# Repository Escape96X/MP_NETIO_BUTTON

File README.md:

# Manual
## How to install on esp8266 with Netio ESP flasher
Best method is to use Visual studio code with plugin Platformio.  
1. Download 'Kód' folder of this repository
2. After installation of VS code and Platformio override esptool.py in platformio
	- Windows path: C:\Users\\**username**\\.platformio\packages\tool-esptoolpy\esptool.py
3. Connect
	- Rx to Tx
	- Tx to Rx
	- GND to GND
	- PROG to PIO0
	- <a href = 'https://github.com/jiricmi/MP_NETIO_BUTTON/issues/14#issuecomment-888953459'>3,3 V to 3,3 V (You have to solder that to R2)</a>
	- <a href = 'https://github.com/jiricmi/MP_NETIO_BUTTON/issues/14#issuecomment-888953459'>RST to ESPEN (solder to RST button)</a>
4. Upload with platformio

<h2>NETIO button tutorial</h2>
<h3>How to set it up</h3>
<ol>
<li>Turn it on with ON/OFF switch</li>
<li>Hold both buttons until red light blinks once.</li>
<li>Open WiFi manager and find <b>NETIO-BUTTON</b> network and search <b>192.168.4.1</b> in internet browser</li>
<li>Under WiFis find your WiFi and click on it after that enter your password</li>
<li>After connecting, copy IP address of the device, reconnect to your network and enter new IP to your browser</li>
</ol>
<h3>Connect to Netio socket</h3>
<ol>
<li>Select <b>Action list</b> on main screen</li>
<li>Click on button <b>add</b></li>
<li>Enter IP adress of Netio socket (only IP without http:// or /netio.json)</li>
<li>Enter JSON string</li>
<li>Choose which button should use this command and submit</li>
<li> You can delete each record in table by clicking on button <b>Delete</b>
<li> On main screen click on button <b>Deep sleep</b> to end <b>conf-mode</b>
</ol>

<h2>Basic info</h2>
<p>
This is prototype of NETIO button that allow you to control the NETIO socket.
It works on sending HTTP request method.
On the other side, this communication is handled by the socket via JSON API. Button is made with small consumption. Button is only up when user sends HTTP request or turns on conf-mode.
</p>
<h3>Device structure</h3>
<p>
Device has 2 buttons with S1 and S2 marks. They are used for <b>JSON configure</b>.
User can program those buttons via conf-mode. <br>
</p>
<h3>LED and buzzer signaling</h3>
<p>
Device has LED with green and red color.
Buzzer is connected with red color of LED.<br>
If <b>green light</b> is on, device is trying to connect to wlan or communicate with the socket. <br>
If <b>red light</b> blinks once for longer time, device entered or quited conf-mode.<br> 
If <b>red light</b> blinks 2x with buzzer signalization, connection to wlan failed. <br>
If <b>red light</b> blinks 3x with buzzer signalization, HTTP communication failed.
Probably IP address of the socket is invalid. <br>
If <b>red light</b> blinks 4x with buzzer signalization, device wasn't able to recognize input. Please hold the button little bit longer.
</p>
<h2>Conf-mode</h2>
<p>
For entering conf-mode, hold both buttons until light turn on for 400ms. After that connect to AP called <b>NETIO-BUTTON</b>. Open browser and search <b>192.168.4.1</b>.
</p>
<h3>WiFi selection</h3>
<p>
On main screen, user is able to connect device to any close-range network without security or with WES, WPA or WPA2-personal. For update WiFi list, click on <b>Scan</b> button. <br>
By clicking on button with your wanted network, you will be transfer to security page (only if network is secured). If password is checked, page will show you IP address of device selected by DHCP server in network. And now you are able to connect to conf-mode via your network and appropriate IP address.
</p>
<h3>IP address of the socket</h3>
<p>
User is able to set 10 IP addresses for each button. So one HTTP request will be send a maximum of 10 devices at once. You can add IP address via form where you also select with button should use this IP address. It is possible to delete each address.
</p>
<h3>JSON message</h3>
<p>
Behind button configure you can find feature to write JSON message to JSON API of socket. Current JSON is below the form.
</p>
<h3>Disable conf-mode button</h3>
<p>This button will put device to sleep. Holding both buttons during conf-mode has same effect.</p>
<h3>Factory reset button</h3>
<p>Deletes whole EEPROM.</p>

# Obsah
📦MP_NETIO_BUTTON  
 ┣ 📂kod - - **Finální program**  
 ┣ 📂dokumentace - **Dokumentace s latex soubory**  
 ┃ ┗ 📜document.pdf   
 ┣ 📂mereni - **Waveform a screenshoty**    
 ┃ ┣ 📂esp32  
 ┃ ┃ ┣ 📂operace  
 ┃ ┃ ┣ 📂ustalene_stavy  
 ┃ ┃ ┗ 📜vysledky_mereni_esp32.xlsx  
 ┃ ┗ 📂esp8266  
 ┃ ┃ ┣ 📂operace  
 ┃ ┃ ┣ 📂ustalene_stavy  
 ┃ ┃ ┗ 📜vysledky_mereni_esp8266.xlsx  
 ┣ 📂navrh_vzorku - **Eagle**    
 ┃ ┣ 📂esp32  
 ┃ ┗ 📂esp8266  
 ┣ 📜.gitignore  
 ┗ 📜README.md  
# Poděkování
*Chtěl bych poděkovat panu učiteli Ing. Břetislavu Bakalovi za odborné vedení práce
a cenné rady, které mi pomohly tuto práci zkompletovat. Rád bych také poděkoval technickému řediteli Ing. Břetislavu Bakalovi ml. společnosti NETIO products a.s. za cenné
rady, věcné připomínky a vstřícnost při konzultacích a vypracování maturitní práce*.
# Úvod maturitní práce
V této maturitní práci porovnám platformy ESP8266 a ESP32 z hlediska spotřeby a reakčního času v takových podmínkách, aby bylo možné určit platformu, která je vhodnější pro funkční vzorek ovladače zásuvek od společnosti NETIO Products a. s. Jelikož je cílem vytvořit co nejvíce úsporné zařízení, jak je jen možné, budu porovnávat jednotlivé ustálené stavy. Zařízení také musí být uživatelsky přívětivé, tzn. není ideální, když
uživatel musí čekat na reakci několik sekund.

Dále na každé platformě porovnám rychlost a spotřebu připojení k WiFi síti a následné odeslání HTTP requestu.
Po vybrání vhodné metody ustáleného stavu, vytvořím konfigurační rozhraní pro editaci nastavení sítě a HTTP requestu, do kterého se bude přistupovat přes access point zařízení ESP.  

Ve finále vytvořím dva funkční koncepty ovladačů pro každou platformu. Tento koncept
bude vycházet z předchozího měření a zjištění. Funkčním vzorkem bude možné ovládat,
buď dvě různé zásuvky, nebo jednu zásuvku z dvěma výstupy. V závěru práce zhodnotím,
zda je možné vytvořit plnohodnotný produkt, či nikoliv.

# Zadání maturitní práce

- V dokumentaci popište technologie NETIO, ESP8266 a ESP32 s ohledem na požadované funkce ovladače
- Navrhněte vhodné uživatelsky přívětivé rozhraní pro konfiguraci ovladače a jeho
připojení do WiFi sítě
- Realizujte požadované funkce na ovladač:
	- vstup na 2 nezávislá tlačítka pro standardní dvojitý přepínač/spínač dvou samostatných zásuvek jednoho zařízení NETIO, eliminace rychlých mačkání (nervózní uživatel)
	- nepodařený příkaz/přepnutí vypínače (nepodaří se odeslat příkaz http) je indikován bliknutím LED a pípnutím buzzeru. Kontroluje se odpověď http serveru (např. 200, 404 návratové hodnoty)
	- Zvolte vhodnou technologii výroby funkčních vzorků (nepájivé pole, DPS) a vyrobte jeden funkční vzorek na bázi ESP8266 a druhý na bázi ESP32 s možností měření odebíraného proudu
	- Určete vhodnou metodu měření dynamické spotřeby energie v čase (reakční doby) pro různé režimy připojení, způsobu komunikace a platformy procesoru:
		- ESP je vypnuto a vzbudí se nějakým externím obvodem přes enable/reset vstup po stisku tlačítka
		- ESP je v deep sleep módu - low power režimu a vzbudí se tlačítkem
 		- ESP je kontinuálně zapnuto
		- Kolik energie spotřebují uvedené režimy při napájení z baterie. Výsledky měření názorně porovnejte
	- Celou dokumentaci včetně výpisů zdrojového programu s komentářem veďte ve verzovacím systému Git a elektronicky doložte k tištěné podobě dokumentace
## Kritéria funkčnosti
- vyrobené vzorky ovladače (ESP8266 a ESP32) jsou funkční
- je vytvořeno uživatelské rozhraní pro konfiguraci ovladač
- bylo provedeno měření spotřeby a doby odezvy pro oba typy ovladače

## Výstupy
- srovnání platforem ESP32 a ESP8266 s ohledem na požadované funkce
- návrh požadovaných funkcí ovladače
- návrh variant ovladače s platformou ESP32 a ESP8266 ve formě ověření konceptu
- zdrojové kódy v repozitáři GIT (GitHub nebo GitLab)
- schéma zapojeni všech zkoušených variant v řešení
- srovnání spotřeby a reakční doby funkčních vzorků

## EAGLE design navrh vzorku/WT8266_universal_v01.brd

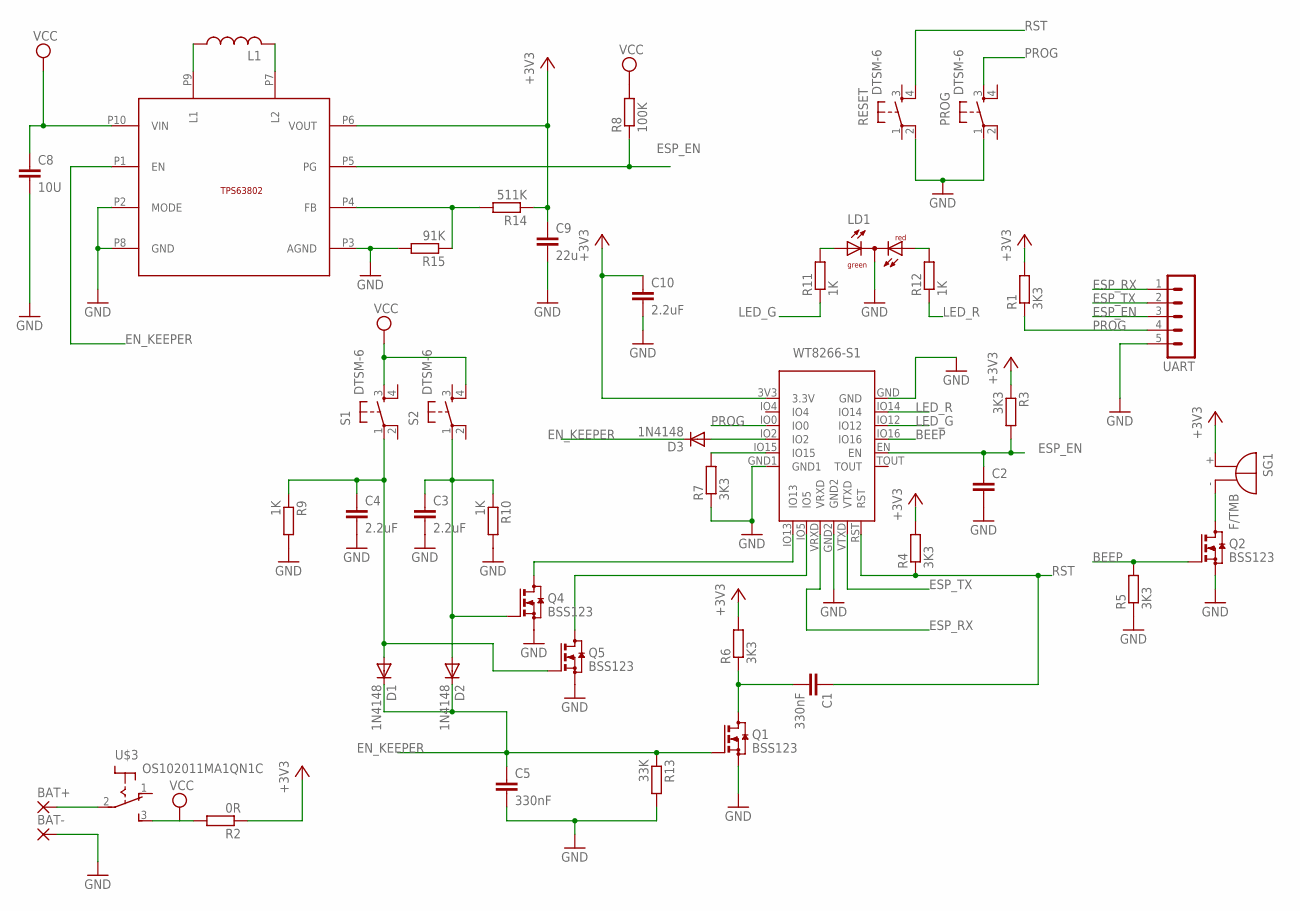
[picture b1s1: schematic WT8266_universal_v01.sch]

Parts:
BAT+: 2,54/1,0
BAT-: 2,54/1,0
C1, C5: 330nF; C0805
C2: C-EUC0805; C0805
C3, C4, C10: 2.2uF; C0805
C8: 10U; C0805
C9: 22u; C0805
D1, D2, D3: 1N4148; 0805
L1: L-USL2825P; L2825P
LD1: DUOLED-RG-C3MM; DUOLED-A-3MM
PROG: DTSM-6
Q1, Q2, Q4, Q5: BSS123; SOT23
R1, R3, R4, R5, R6, R7: 3K3; R0805
R2: 0R; R0805
R8: 100K; R0805
R9, R10, R11, R12: 1K; R0805
R13: 33K; R0805
R14: 511K; R0805
R15: 91K; R0805
RESET: DTSM-6
S1, S2: DTSM-6
SG1: F/TMB
U$1: WT8266-S1
U$3: OS102011MA1QN1C
U$4: TPS63802; VSON-HR-10
UART: MAR05-1

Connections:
+3V3: C9.1, C10.1, R1.2, R2.1, R3.1, R4.2, R6.2, R14.1, SG1.+, U$1.3V3 (3.3V), U$4.P6 (VOUT)
BEEP: Q2.1 (G), R5.2, U$1.IO16
EN_KEEPER: C5.1, D1.1 (C), D2.1 (C), D3.1 (C), Q1.1 (G), R13.1, U$4.P1 (EN)
ESP_EN: C2.1, R3.2, R8.1, U$1.EN, U$4.P5 (PG), UART.3
ESP_RX: U$1.VRXD, UART.1
ESP_TX: U$1.VTXD, UART.2
GND: BAT-.1, C2.2, C3.2, C4.2, C5.2, C8.2, C9.2, C10.2, LD1.2 (C), PROG.1, Q1.2 (S), Q2.2 (S), Q4.2 (S), Q5.2 (S), R5.1, R7.1, R9.2, R10.2, R13.2, R15.2, RESET.2, U$1.GND, U$1.GND1, U$1.GND2, U$4.P2 (MODE), U$4.P3 (AGND), U$4.P8 (GND), UART.5
LED_G: R11.1, U$1.IO12
LED_R: R12.1, U$1.IO14
unnamed: R14.2, R15.1, U$4.P4 (FB)
unnamed: C1.2, Q1.3 (D), R6.1
unnamed: R7.2, U$1.IO15
unnamed: D3.2 (A), U$1.IO2
unnamed: Q4.3 (D), U$1.IO13
unnamed: Q5.3 (D), U$1.IO5
unnamed: LD1.1 (AG), R11.2
unnamed: Q2.3 (D), SG1.-
unnamed: BAT+.1, U$3.2
unnamed: C3.1, D2.2 (A), Q4.1 (G), R10.1, S2.1
unnamed: L1.1, U$4.P9 (L1)
unnamed: C4.1, D1.2 (A), Q5.1 (G), R9.1, S1.1
unnamed: L1.2, U$4.P7 (L2)
unnamed: LD1.3 (AR), R12.2
PROG: PROG.3, R1.1, U$1.IO0, UART.4
RST: C1.1, R4.1, RESET.4, U$1.RST
VCC: C8.1, R2.2, R8.2, S1.3, S2.4, U$3.3 (S), U$4.P10 (VIN)

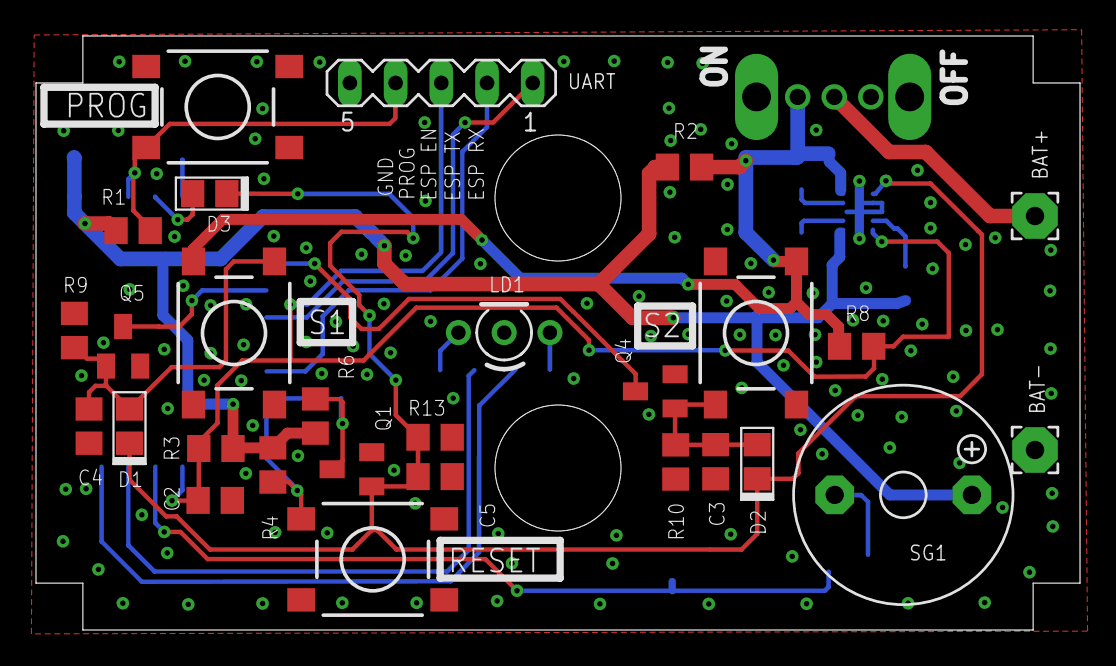
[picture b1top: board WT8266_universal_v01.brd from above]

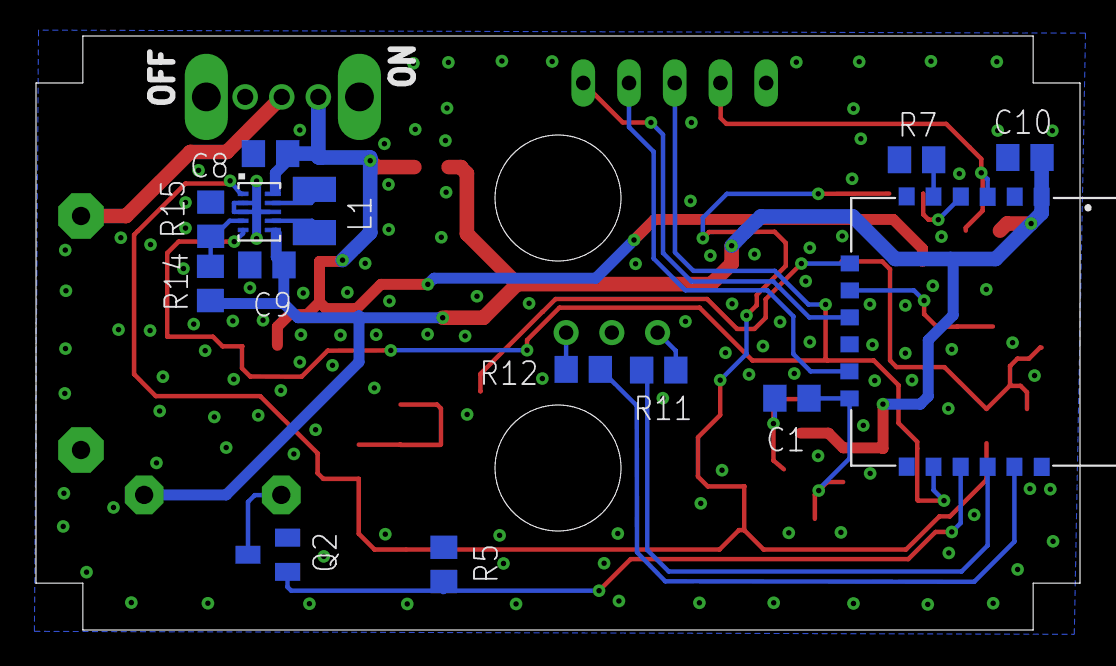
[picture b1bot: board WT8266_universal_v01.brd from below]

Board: 2 copper layers, 58.0 x 33.0 mm, 43 parts (14 on the bottom side), 26 nets.

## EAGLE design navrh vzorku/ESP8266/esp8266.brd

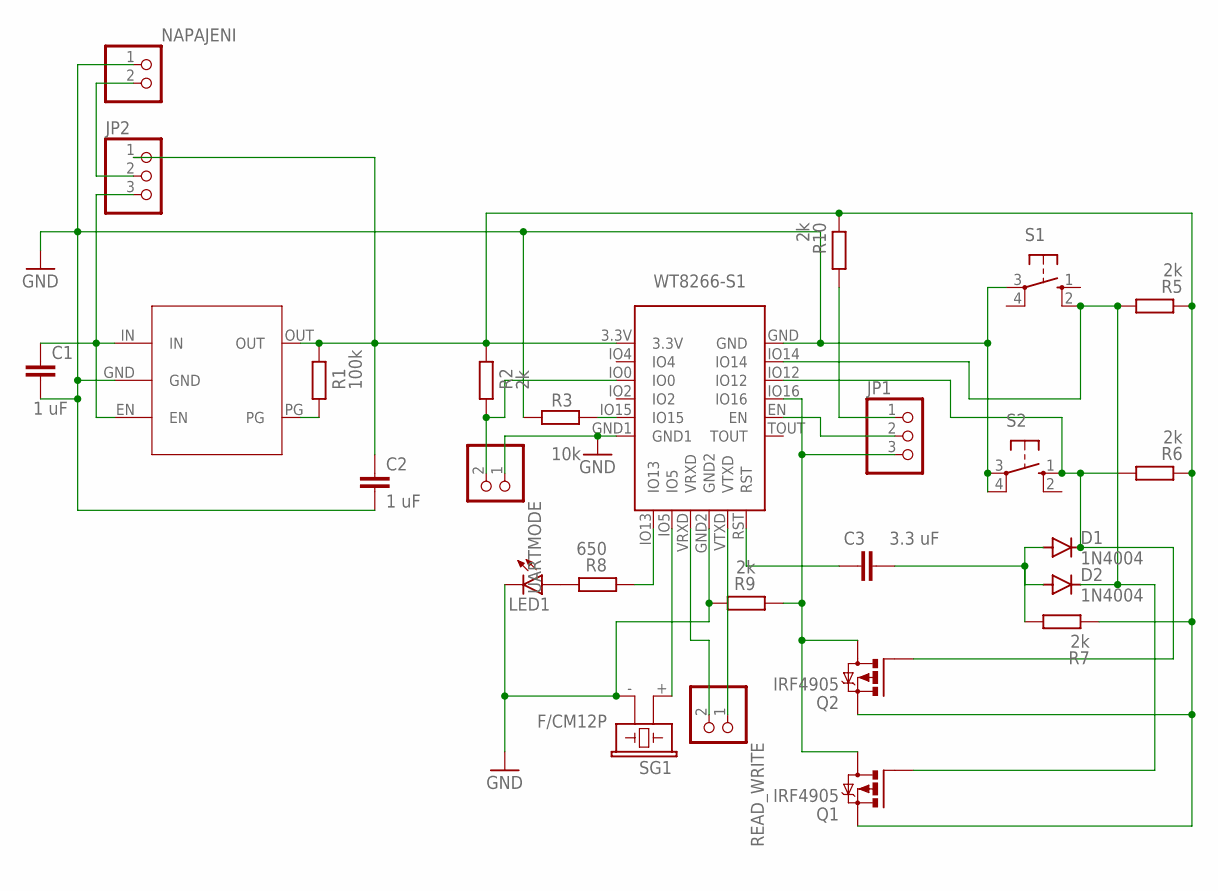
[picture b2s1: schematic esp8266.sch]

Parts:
C1, C2: 1 uF; C2.5-2
C3: 3.3 uF; C2.5-2
D1, D2: 1N4004; DO41-10
JP1, JP2: PINHD-1X3; 1X03
LED1: LED5MM
NAPAJENI: PINHD-1X2; 1X02
Q1, Q2: IRF4905; TO220BH
R1: 100k; 0207/10
R2, R5, R6, R7, R9, R10: 2k; 0207/10
R3: 10k; 0207/10
R8: 650; 0207/10
READ_WRITE: PINHD-1X2; 1X02
S1, S2: 10-XX; B3F-10XX
SG1: F/CM12P
U$1: WT8266-S1
U$2: LDLN030
UARTMODE: PINHD-1X2; 1X02

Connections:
GND: C1.2, C2.2, LED1.K (C), NAPAJENI.1, R3.1, R9.2, S1.3, S2.3, S2.4 (P1), SG1.- (2), U$1.GND, U$1.GND1, U$1.GND2, U$2.GND, UARTMODE.1
unnamed: C1.1, JP2.3, U$2.EN, U$2.IN
unnamed: JP2.2, NAPAJENI.2
unnamed: R2.1, U$1.IO0, UARTMODE.2
unnamed: R1.1, U$2.PG
unnamed: READ_WRITE.2, U$1.VRXD
unnamed: C2.1, JP2.1, Q1.S, Q2.S, R1.2, R2.2, R5.1, R6.1, R7.1, R10.1, U$1.3.3V, U$2.OUT
unnamed: READ_WRITE.1, U$1.VTXD
unnamed: R3.2, U$1.IO15
unnamed: C3.1, U$1.RST
unnamed: D1.C, Q2.G, R6.2, S2.1 (S), U$1.IO12
unnamed: D2.C, Q1.G, R5.2, S1.2 (S1), U$1.IO14
unnamed: C3.2, D1.A, D2.A, R7.2
unnamed: R8.1, U$1.IO13
unnamed: LED1.A, R8.2
unnamed: SG1.+ (1), U$1.IO5
unnamed: JP1.3, Q1.D, Q2.D, R9.1, U$1.IO16
unnamed: JP1.2, U$1.EN
unnamed: JP1.1, R10.2

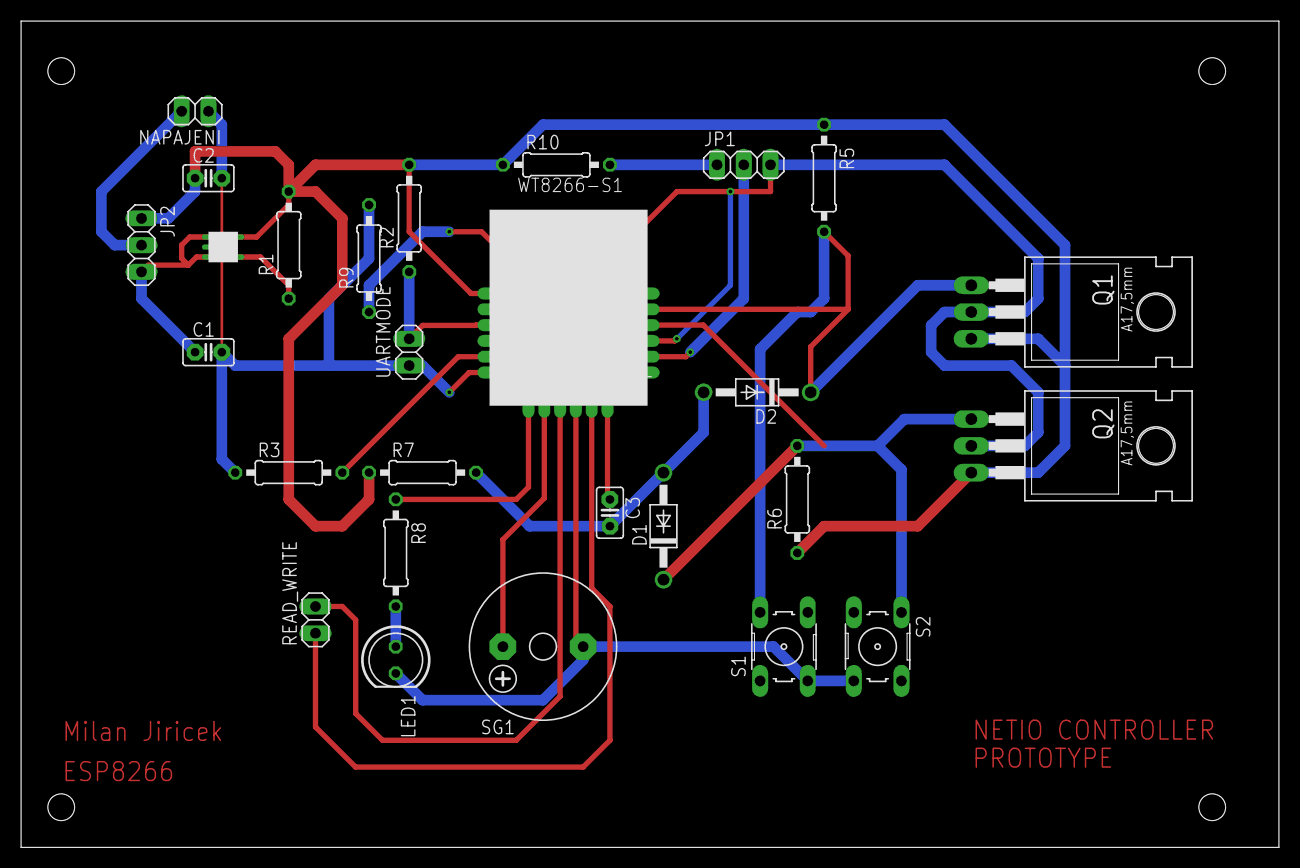
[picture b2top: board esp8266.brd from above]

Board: 2 copper layers, 119.4 x 78.4 mm, 27 parts (0 on the bottom side), 19 nets.

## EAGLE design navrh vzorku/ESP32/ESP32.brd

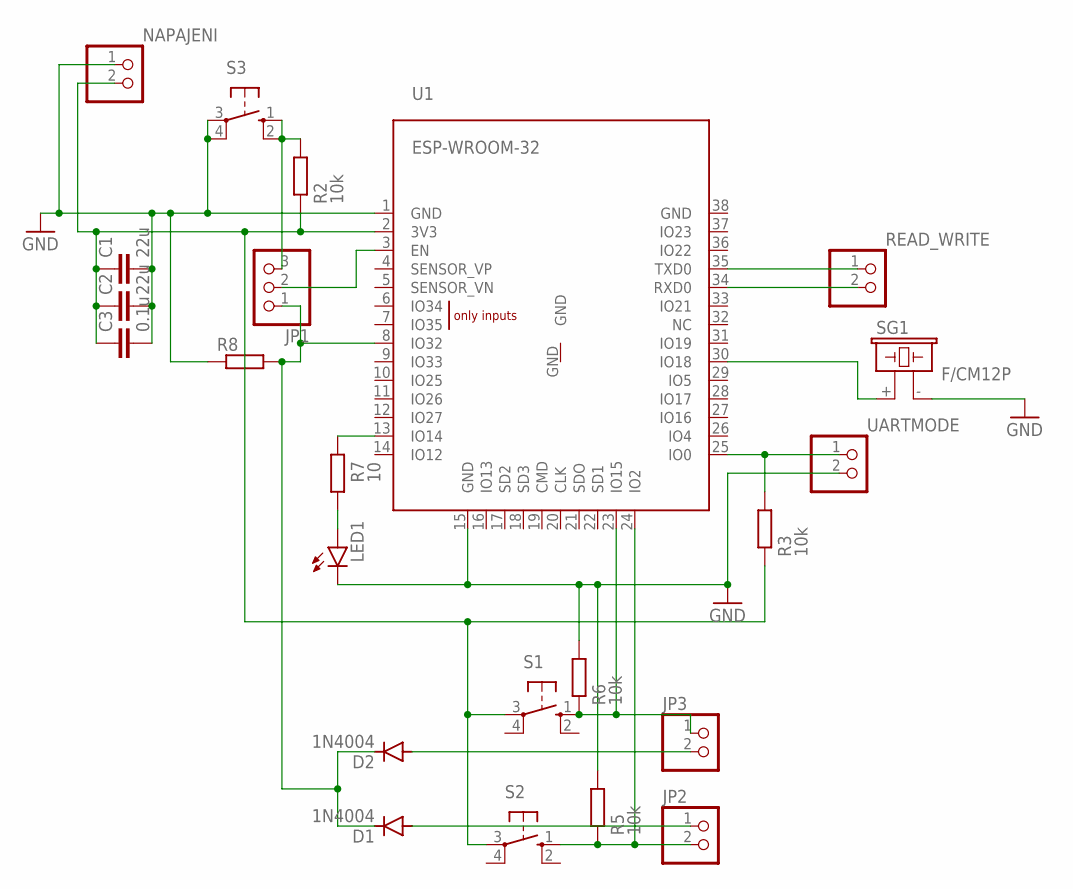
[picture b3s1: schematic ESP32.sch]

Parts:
C1, C2: 22u; C2.5-2
C3: 0.1u; C2.5-2
D1, D2: 1N4004; DO41-10
JP1: PINHD-1X3; 1X03
JP2, JP3: PINHD-1X2; 1X02
LED1: LED5MM
NAPAJENI: PINHD-1X2; 1X02
R2, R3, R5, R6: 10k; 0207/10
R7: 10; 0207/10
R8: R-EU_0207/10; 0207/10
READ_WRITE: PINHD-1X2; 1X02
S1, S2, S3: 10-XX; B3F-10XX
SG1: F/CM12P
U1: ESP-WROOM-32
UARTMODE: PINHD-1X2; 1X02

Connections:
GND: C1.2, C2.2, C3.2, LED1.K (C), NAPAJENI.1, R5.2, R6.2, R8.1, S3.3, S3.4 (P1), SG1.- (2), U1.1 (GND), U1.15 (GND), UARTMODE.2
unnamed: SG1.+ (1), U1.30 (IO18)
unnamed: C1.1, C2.1, C3.1, NAPAJENI.2, R2.1, R3.1, S1.3, S2.3, U1.2 (3V3)
unnamed: JP1.3, R2.2, S3.1 (S), S3.2 (S1)
unnamed: JP1.2, U1.3 (EN)
unnamed: READ_WRITE.2, U1.34 (RXD0)
unnamed: READ_WRITE.1, U1.35 (TXD0)
unnamed: R3.2, U1.25 (IO0), UARTMODE.1
unnamed: JP2.2, R5.1, S2.1 (S), U1.24 (IO2)
unnamed: JP3.1, R6.1, S1.1 (S), U1.23 (IO15)
unnamed: R7.2, U1.13 (IO14)
unnamed: LED1.A, R7.1
unnamed: D1.C, D2.C, JP1.1, R8.2, U1.8 (IO32)
unnamed: D1.A, JP2.1
unnamed: D2.A, JP3.2

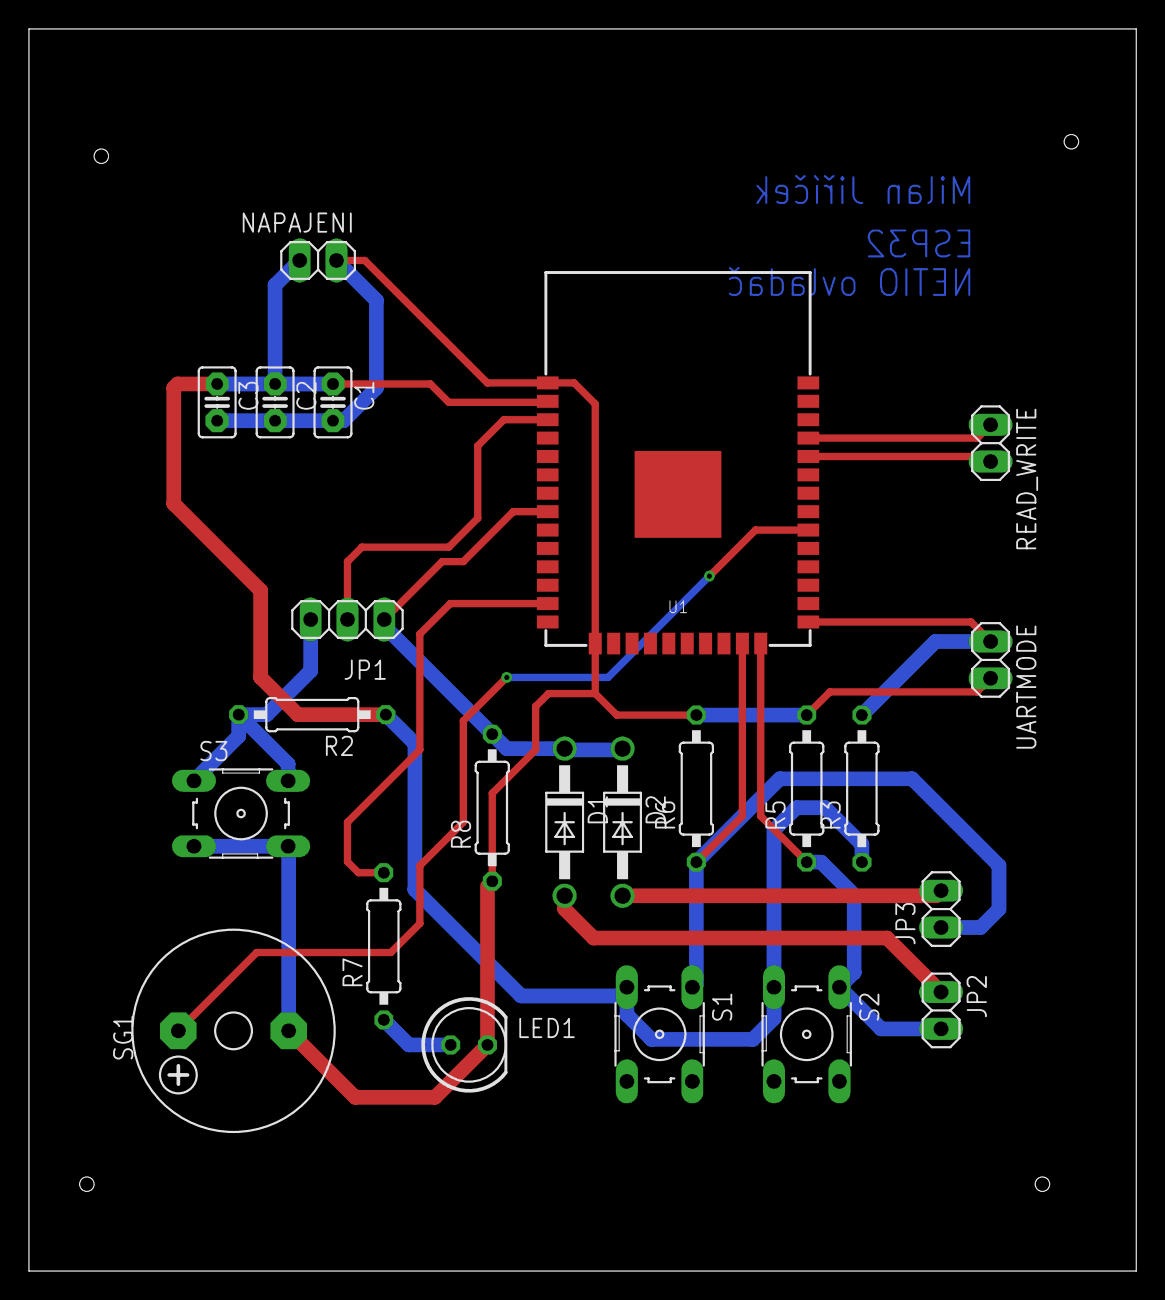
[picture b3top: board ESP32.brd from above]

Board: 2 copper layers, 76.5 x 85.8 mm, 23 parts (0 on the bottom side), 15 nets.

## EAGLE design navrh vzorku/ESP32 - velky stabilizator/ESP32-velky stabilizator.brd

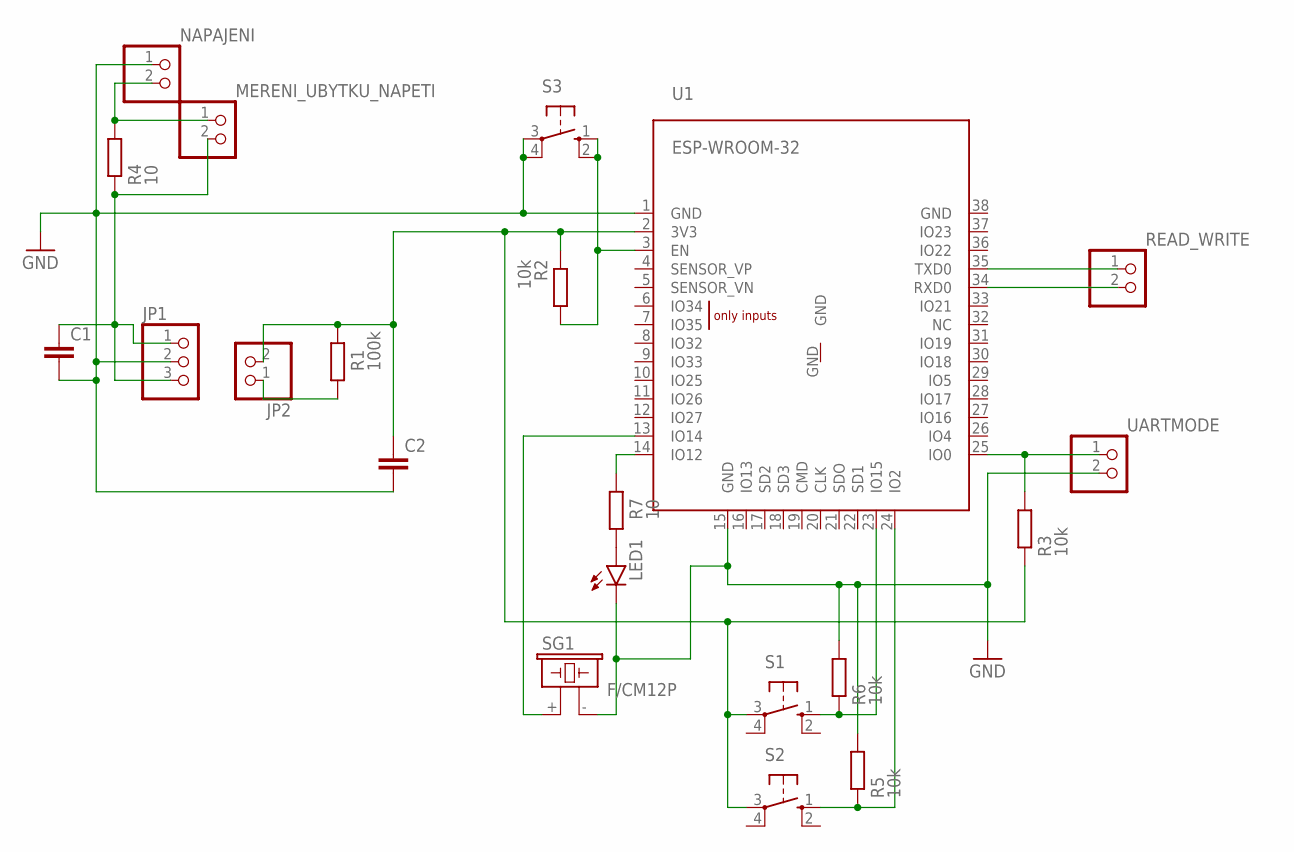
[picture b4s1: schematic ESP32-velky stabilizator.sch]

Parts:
C1, C2: C2.5/2; C2.5-2
JP1: PINHD-1X3; 1X03
JP2: PINHD-1X2; 1X02
LED1: LED5MM
MERENI_UBYTKU_NAPETI: PINHD-1X2; 1X02
NAPAJENI: PINHD-1X2; 1X02
R1: 100k; 0207/10
R2, R3, R5, R6: 10k; 0207/10
R4, R7: 10; 0207/10
READ_WRITE: PINHD-1X2; 1X02
S1, S2, S3: 10-XX; B3F-10XX
SG1: F/CM12P
U1: ESP-WROOM-32
UARTMODE: PINHD-1X2; 1X02

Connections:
GND: C1.2, C2.2, JP1.2, LED1.K (C), NAPAJENI.1, R5.2, R6.2, S3.3, S3.4 (P1), SG1.- (2), U1.1 (GND), U1.15 (GND), UARTMODE.2
unnamed: C1.1, JP1.1, JP1.3, MERENI_UBYTKU_NAPETI.2, R4.1
unnamed: C2.1, JP2.2, R1.2, R2.1, R3.1, S1.3, S2.3, U1.2 (3V3)
unnamed: JP2.1, R1.1
unnamed: R2.2, S3.1 (S), S3.2 (S1), U1.3 (EN)
unnamed: READ_WRITE.2, U1.34 (RXD0)
unnamed: READ_WRITE.1, U1.35 (TXD0)
unnamed: R3.2, U1.25 (IO0), UARTMODE.1
unnamed: R7.2, U1.14 (IO12)
unnamed: MERENI_UBYTKU_NAPETI.1, NAPAJENI.2, R4.2
unnamed: R5.1, S2.1 (S), U1.24 (IO2)
unnamed: R6.1, S1.1 (S), U1.23 (IO15)
unnamed: SG1.+ (1), U1.13 (IO14)
unnamed: LED1.A, R7.1

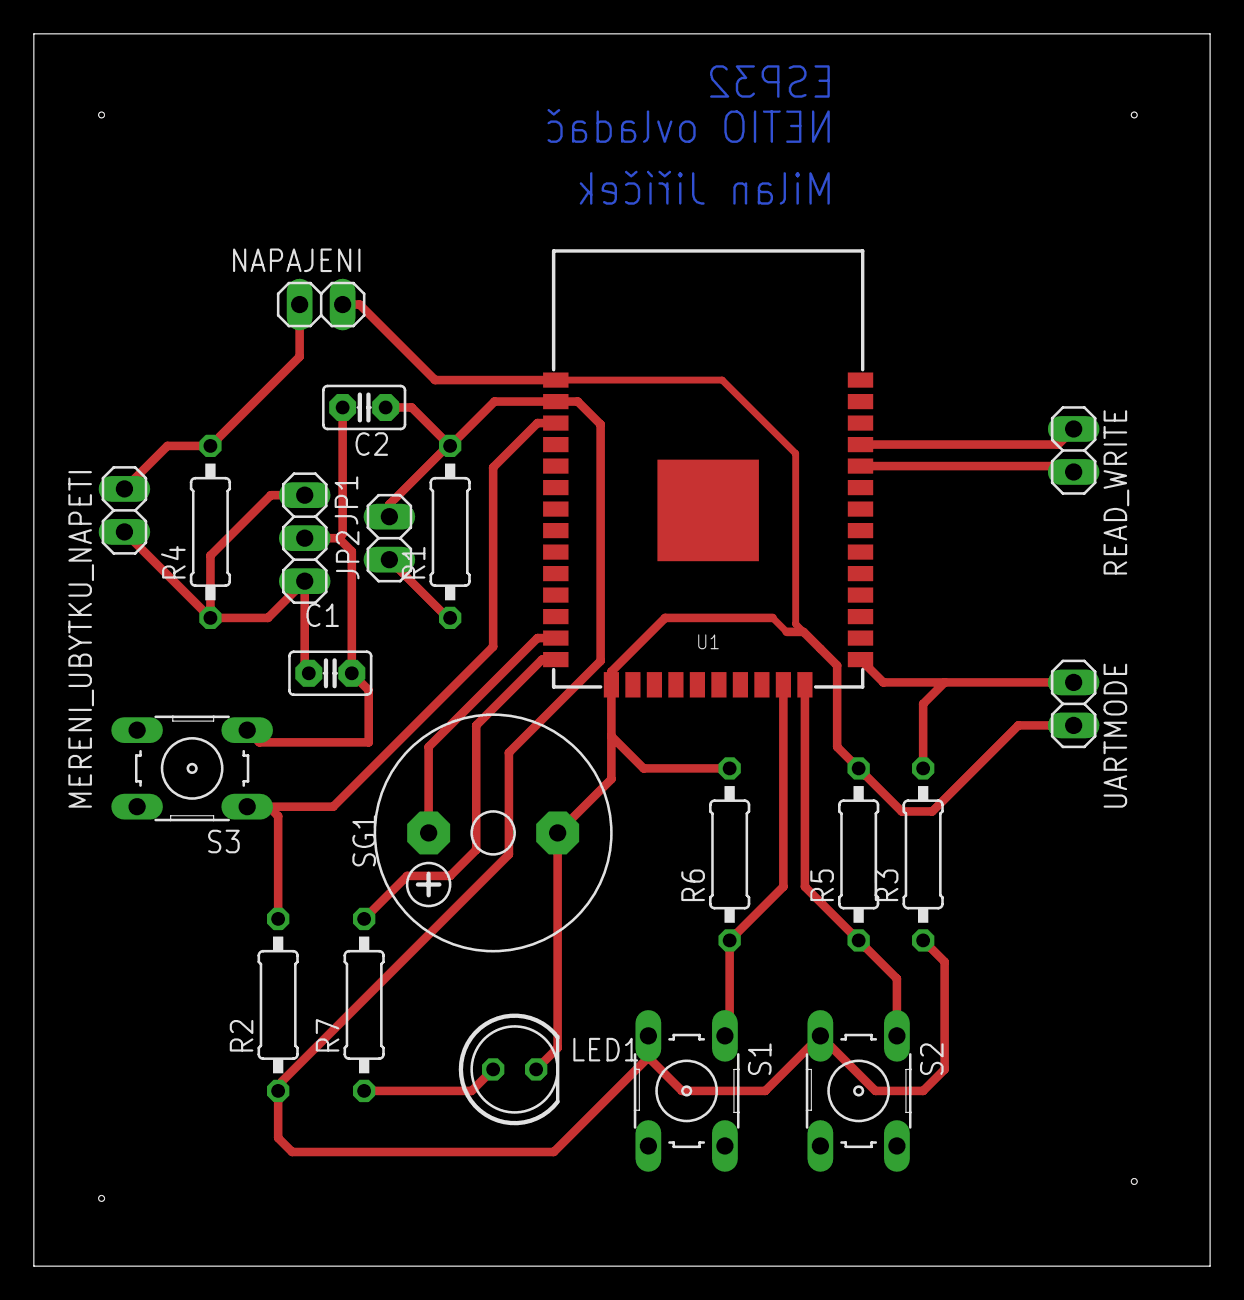
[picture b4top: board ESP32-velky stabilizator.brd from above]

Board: 2 copper layers, 69.5 x 72.8 mm, 21 parts (0 on the bottom side), 14 nets.

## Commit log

2020-09-22 Pridano zadani a button-ESP8266.ino a button-ESP32
2020-09-22 sketch.ino move to directory
2020-09-23 Dokumentace, Datasheets, README
2020-09-25 add description JSON-NETIO-M2M-API_interface
2020-09-26 add NodeRed-controll_Netio4All
2020-09-28 ESP8266 MQTT BROKER IN PROGRESS
2020-10-04 HTTP
2020-10-07 comments
2020-10-17 updateBA1
2020-10-17 Upravené chyby v dokumentaci
2020-10-17 finalni zadani
2020-10-20 finalni dokumentace
2020-10-20 add_datasheet_UART/USB-CP2102
2020-10-22 Dokumentace v latexu
2020-10-22 Dokumentace Latex
2020-10-22 README a TODO
2020-10-25 poznamky v todo
2020-10-26 Refactoring
2020-10-27 Schéma UART a enable
2020-10-28 ENABLE, Kontinualni
2020-11-01 deep sleep
2020-11-03 Schema opraveno
2020-11-05 Algoritmus
2020-11-11 Úklid
2020-11-16 vyvoj webserveru-wifi
2020-11-18 pripojeni na wifi
2020-11-24 Implementace wifi do ESP
2020-11-29 EEPROM MEMORY
2020-12-01 configurace Tlacitek
2020-12-04 buttonconfig
2020-12-07 Návod k použití
2020-12-15 Redukce board
2020-12-21 Měření 8266
2020-12-22 Tištěné spoje redukce
2020-12-29 Dokumentace o měření
2021-01-04 Latex
2021-01-06 Měření WiFi
2021-01-06 WPA2 mereni
2021-01-11 Kontinualní měření
2021-01-18 Klidové režimy
2021-01-21 ESP8266
2021-01-21 Dokumentace popis ESP8266
2021-01-23 Refactoring dokumentace
2021-01-26 dokumentace - Měření spotřeby operací
2021-01-29 ESP32 CODE
2021-01-29 ESP32 CODE1
2021-02-04 ESP8266 DEEP SLEEP TEORIE
2021-02-05 Dokumentace tvorba webu
2021-02-12 ESP32 měřené
2021-02-14 Zapsání výsledků měření
2021-02-16 dokumentace
2021-02-16 Dokumentace zas a znova
2021-02-17 Dokumentace mereni esp8266
2021-02-22 EAGLE vzorek
2021-02-28 Funkcni vzorky eagle
2021-03-04 Program funčního vzorku ESP
2021-03-07 funkcni vzorek ESP8266
2021-03-08 Dokumetace tvorba esp8266 vzorku
2021-03-10 Plosne spoje
2021-03-14 LATEX DOKUMENTACE
2021-03-16 test
2021-03-29 SOC soutez
2021-04-10 Finalni verze
2021-04-15 Finální verze
2021-07-16 ip adress table
2021-07-21 IP table
2021-07-22 debugging and adding features
2021-07-23 linux tranfer
2021-07-28 HTTP table
2021-07-28 Manual
2021-07-29 buzzer
2021-07-29 debugging
2021-07-29 debuging
2021-07-29 New menu
2021-08-04 refactor
2021-08-27 fixing wifi connection
2021-12-06 zacatek
2022-02-07 uprava
2022-02-10 loging
2022-02-10 basic settings
2022-02-16 config fs
2022-02-16 Testing LittleFS
2022-02-23 json parser test
2022-03-22 pokus o nove menu
2022-03-22 oprava chyby
2022-10-24 -esptool
